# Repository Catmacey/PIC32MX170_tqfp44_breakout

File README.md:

Breakout for PIC32MX170 in 44pin TQFP package
=============================

This is a simple "inline" breakout for using the 44pin TQFP package in a breadboard.
The board contains the bare minimum support passives to get the PIC running.

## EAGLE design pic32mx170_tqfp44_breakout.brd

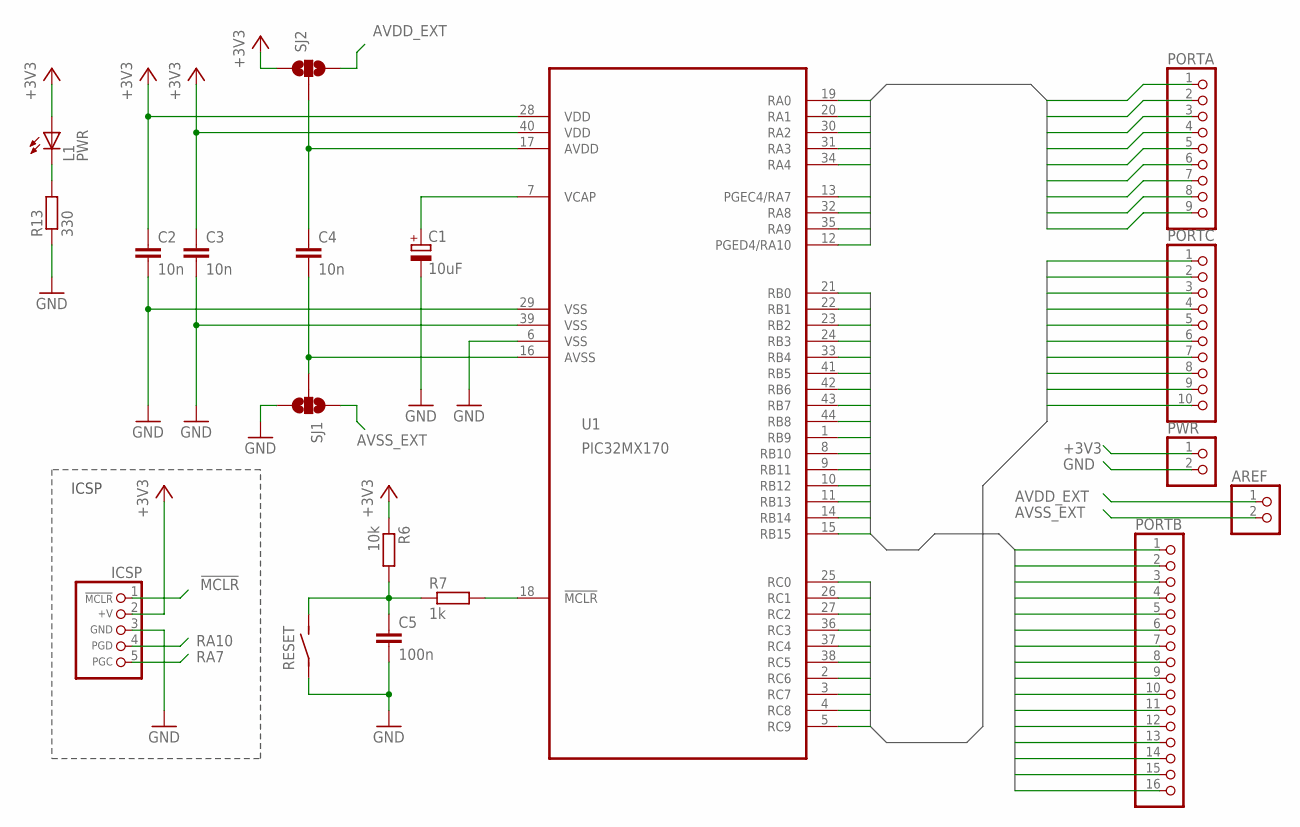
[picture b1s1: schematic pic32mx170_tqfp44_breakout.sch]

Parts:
AREF: PINHD-1X2; 1X02
C1: 10uF; SMC_A
C2, C3, C4: 10n; C0805
C5: 100n; C0805
ICSP: CON_HEADER_PRG_PIC_ICSPB; HEADER_PRG_1X05_ICSP_B
L1: PWR; LED-805
PORTA: PINHD-1X9; 1X09
PORTB: PINHD-1X16; 1X16
PORTC: PINHD-1X10; 1X10
PWR: PINHD-1X2; 1X02
R6: 10k; R0805
R7: 1k; R0805
R13: 330; R0805
RESET: ITT-PTS645S
SJ1, SJ2: SOLDERJUMPER_2WAYS; SJ_3
U1: PIC32MX170; TQFP44

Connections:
!MCLR: ICSP.1 (/MCLR), R7.2, U1.18 (!MCLR)
+3V3: C2.1, C3.1, ICSP.2 (+V), L1.A, PWR.1, R6.1, SJ2.1, U1.28 (VDD), U1.40 (VDD)
AVDD: C4.1, SJ2.2, U1.17 (AVDD)
AVDD_EXT: AREF.1, SJ2.3
AVSS: C4.2, SJ1.2, U1.16 (AVSS)
AVSS_EXT: AREF.2, SJ1.1
GND: C1.-, C2.2, C3.2, C5.2, ICSP.3 (GND), PWR.2, R13.1, RESET.P$1 (1), RESET.P$2 (1), SJ1.3, U1.6 (VSS), U1.29 (VSS), U1.39 (VSS)
unnamed: C1.+, U1.7 (VCAP)
unnamed: L1.C, R13.2
RA0: PORTA.1, U1.19 (RA0)
RA1: PORTA.2, U1.20 (RA1)
RA2: PORTA.3, U1.30 (RA2)
RA3: PORTA.4, U1.31 (RA3)
RA4: PORTA.5, U1.34 (RA4)
RA7: ICSP.5 (PGC), PORTA.6, U1.13 (PGEC4/RA7)
RA8: PORTA.7, U1.32 (RA8)
RA9: PORTA.8, U1.35 (RA9)
RA10: ICSP.4 (PGD), PORTA.9, U1.12 (PGED4/RA10)
RB0: PORTB.1, U1.21 (RB0)
RB1: PORTB.2, U1.22 (RB1)
RB2: PORTB.3, U1.23 (RB2)
RB3: PORTB.4, U1.24 (RB3)
RB4: PORTB.5, U1.33 (RB4)
RB5: PORTB.6, U1.41 (RB5)
RB6: PORTB.7, U1.42 (RB6)
RB7: PORTB.8, U1.43 (RB7)
RB8: PORTB.9, U1.44 (RB8)
RB9: PORTB.10, U1.1 (RB9)
RB10: PORTB.11, U1.8 (RB10)
RB11: PORTB.12, U1.9 (RB11)
RB12: PORTB.13, U1.10 (RB12)
RB13: PORTB.14, U1.11 (RB13)
RB14: PORTB.15, U1.14 (RB14)
RB15: PORTB.16, U1.15 (RB15)
RC0: PORTC.1, U1.25 (RC0)
RC1: PORTC.2, U1.26 (RC1)
RC2: PORTC.3, U1.27 (RC2)
RC3: PORTC.4, U1.36 (RC3)
RC4: PORTC.5, U1.37 (RC4)
RC5: PORTC.6, U1.38 (RC5)
RC6: PORTC.7, U1.2 (RC6)
RC7: PORTC.8, U1.3 (RC7)
RC8: PORTC.9, U1.4 (RC8)
RC9: PORTC.10, U1.5 (RC9)
RESET: C5.1, R6.2, R7.1, RESET.P$3 (2), RESET.P$4 (2)

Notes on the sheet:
ICSP

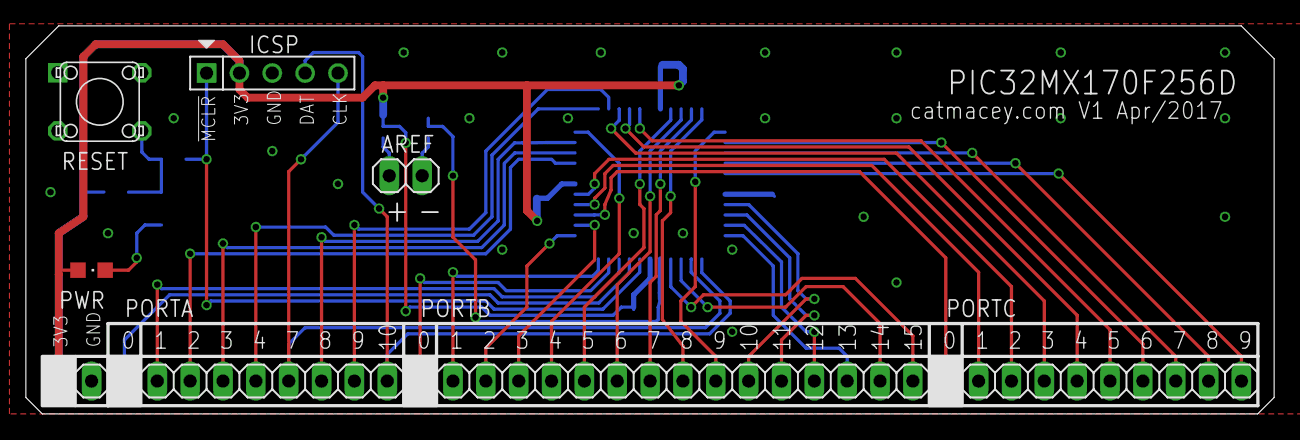
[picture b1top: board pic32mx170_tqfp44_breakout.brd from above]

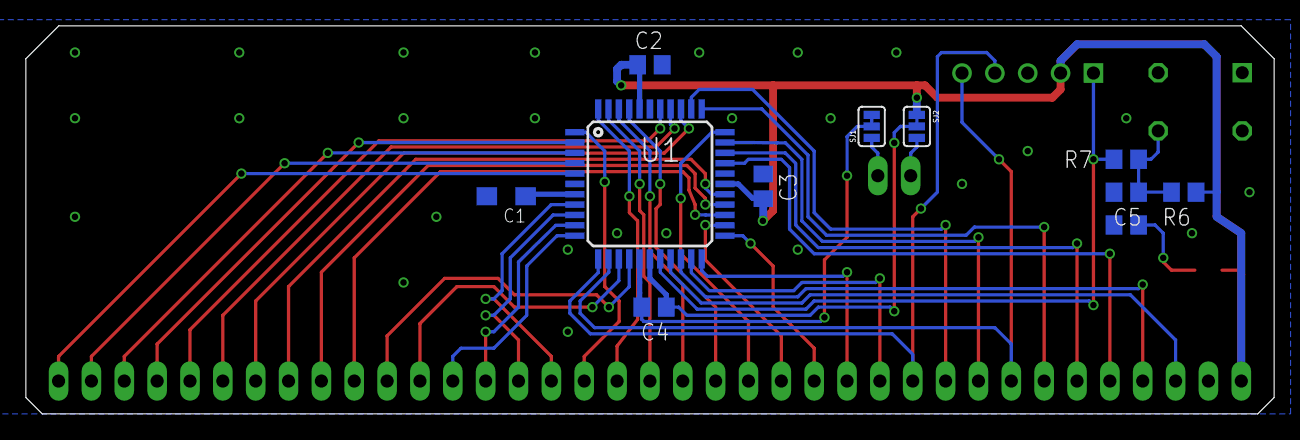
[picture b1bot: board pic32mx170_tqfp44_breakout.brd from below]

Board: 2 copper layers, 96.5 x 30.0 mm, 19 parts (11 on the bottom side), 45 nets.

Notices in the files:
parts and their libraries:
SparkFun: Licensing: CC v3.0 Share-Alike You are welcome to use this library for commercial purposes.
